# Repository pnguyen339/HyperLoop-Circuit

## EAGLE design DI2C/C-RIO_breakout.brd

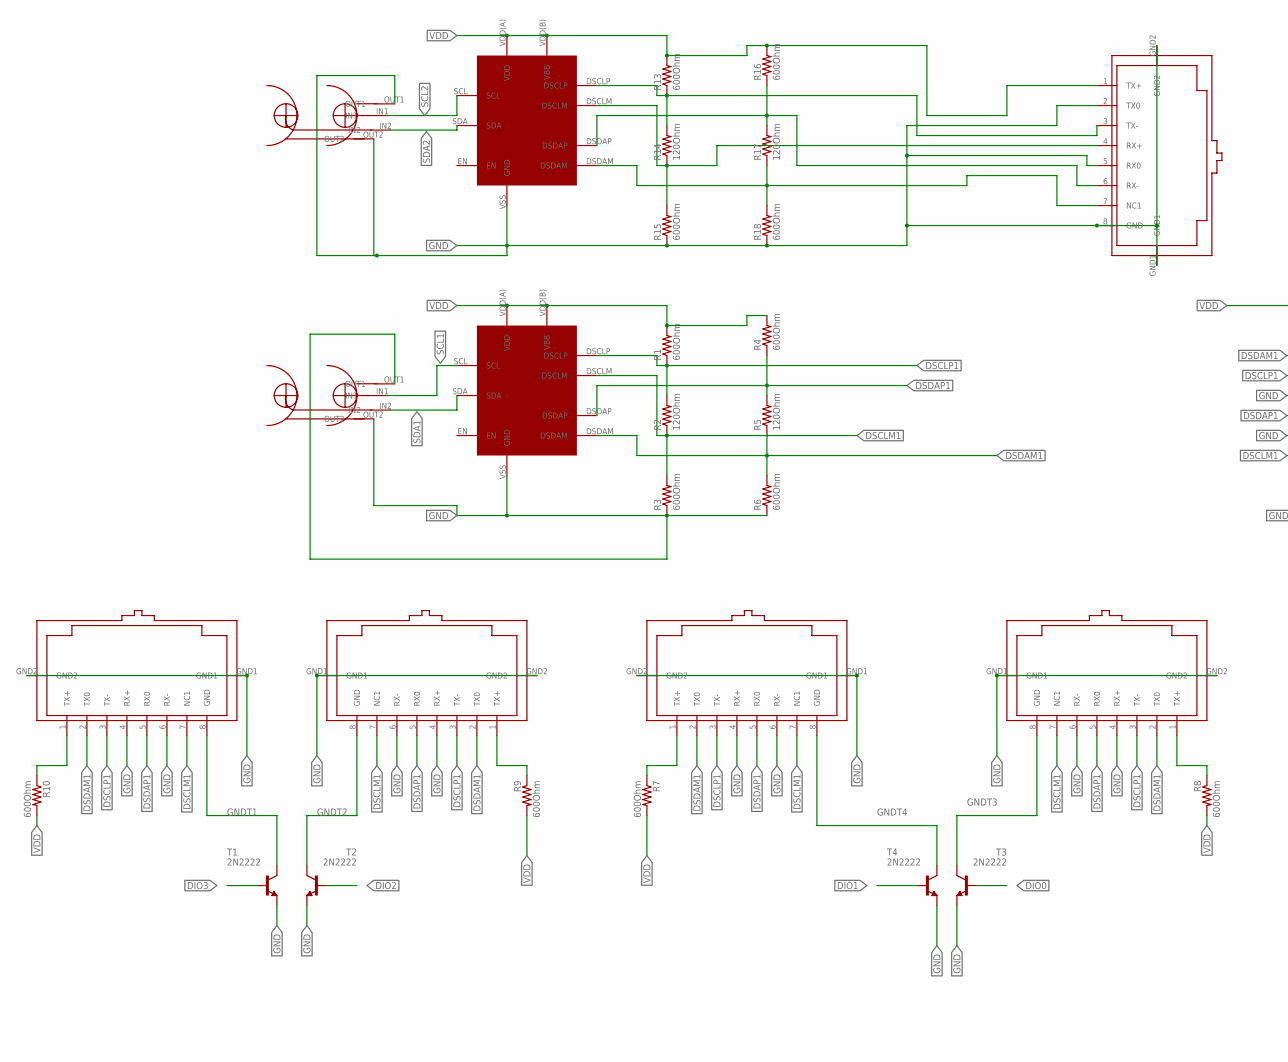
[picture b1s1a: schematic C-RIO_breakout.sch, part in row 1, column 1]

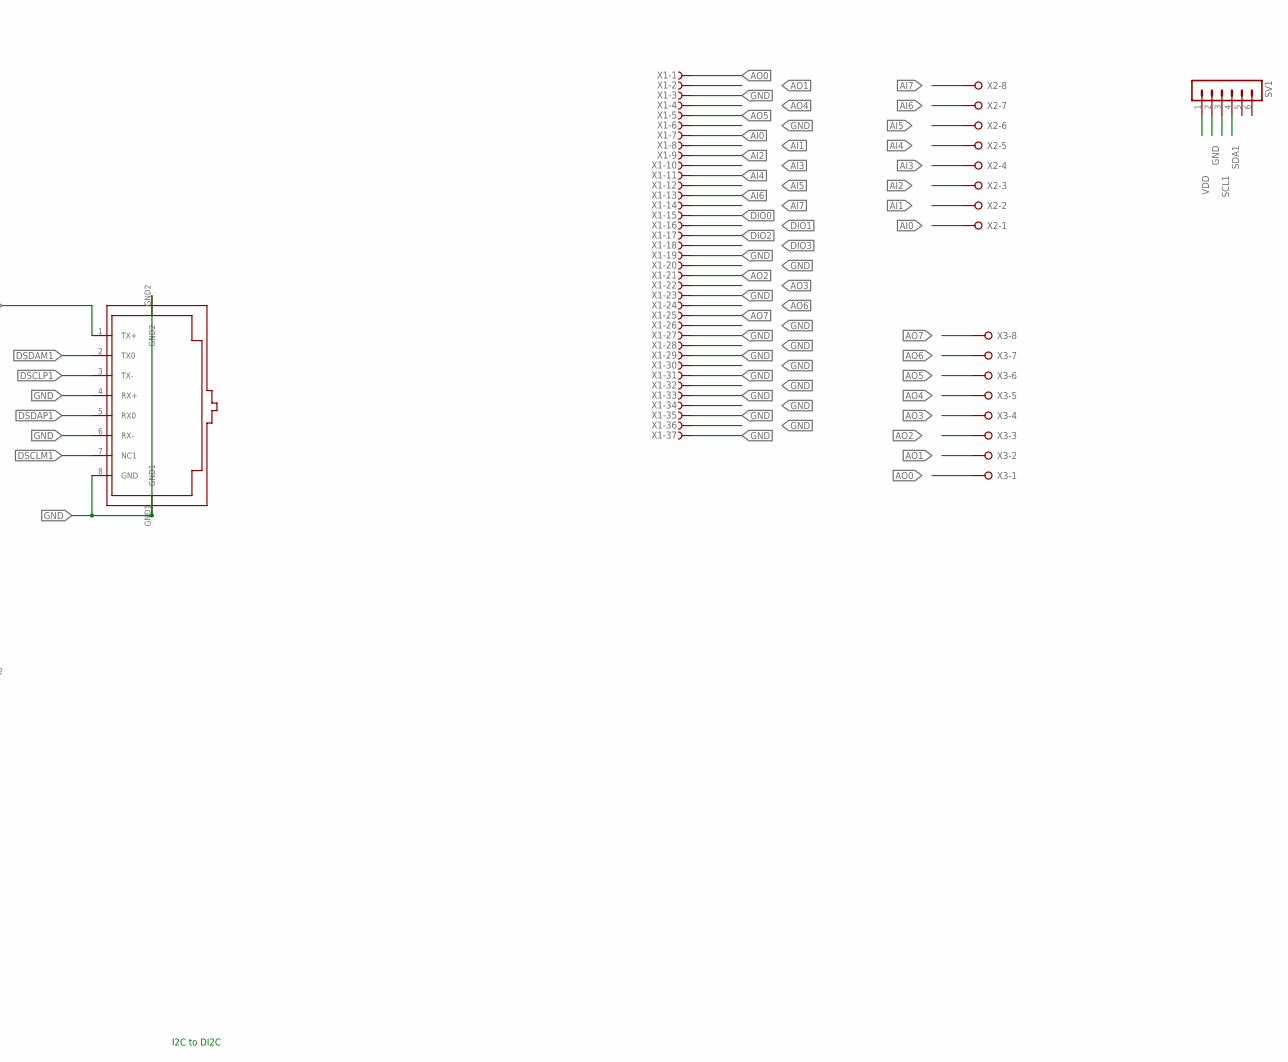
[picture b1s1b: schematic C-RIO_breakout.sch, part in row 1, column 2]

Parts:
COMMON: RJ45-8N4-B
R1, R3, R4, R6, R7, R8, R9, R10, R13, R15, R16, R18: 600Ohm; 0414/15
R2, R5, R14, R17: 120Ohm; 0414/15
SV1: MA06-1
T1, T2, T3, T4: 2N2222; TO18
TOF1, TOF2, TOF3, TOF4: RJ45-8N4-B
U$1, U$3: PCA9615
U$2, U$4: DUALBNC_CONNECTOR
U$6: RJ45-8N4-B
X1: F37HPS; F37HP
X2, X3: W237-08P; W237-8P

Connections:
AI0: X1.7, X2.1
AI1: X1.8, X2.2
AI2: X1.9, X2.3
AI3: X1.10, X2.4
AI4: X1.11, X2.5
AI5: X1.12, X2.6
AI6: X1.13, X2.7
AI7: X1.14, X2.8
AO0: X1.1, X3.1
AO1: X1.2, X3.2
AO2: X1.21, X3.3
AO3: X1.22, X3.4
AO4: X1.4, X3.5
AO5: X1.5, X3.6
AO6: X1.24, X3.7
AO7: X1.25, X3.8
DIO0: T3.2 (B), X1.15
DIO1: T4.2 (B), X1.16
DIO2: T2.2 (B), X1.17
DIO3: T1.2 (B), X1.18
DSCLM1: COMMON.7 (NC1), R2.1, R3.2, TOF1.7 (NC1), TOF2.7 (NC1), TOF3.7 (NC1), TOF4.7 (NC1), U$1.DSCLM
DSCLP1: COMMON.3 (TX-), R1.1, R2.2, TOF1.3 (TX-), TOF2.3 (TX-), TOF3.3 (TX-), TOF4.3 (TX-), U$1.DSCLP
DSDAM1: COMMON.2 (TX0), R5.1, R6.2, TOF1.2 (TX0), TOF2.2 (TX0), TOF3.2 (TX0), TOF4.2 (TX0), U$1.DSDAM
DSDAP1: COMMON.5 (RX0), TOF1.5 (RX0), TOF2.5 (RX0), TOF3.5 (RX0), TOF4.5 (RX0)
GND: COMMON.4 (RX+), COMMON.6 (RX-), COMMON.8 (GND), COMMON.GND1, COMMON.GND2, R3.1, R6.1, R15.1, R18.1, SV1.2, T1.1 (E), T2.1 (E), T3.1 (E), T4.1 (E), TOF1.4 (RX+), TOF1.6 (RX-), TOF2.4 (RX+), TOF2.6 (RX-), TOF3.4 (RX+), TOF3.6 (RX-), TOF4.4 (RX+), TOF4.6 (RX-), U$1.VSS (GND), U$2.OUT1, U$2.OUT2, U$3.VSS (GND), U$4.OUT1, U$4.OUT2, U$6.2 (TX0), U$6.5 (RX0), U$6.8 (GND), U$6.GND1, U$6.GND2, X1.3, X1.6, X1.19, X1.20, X1.23, X1.26, X1.27, X1.28, X1.29, X1.30, X1.31, X1.32, X1.33, X1.34, X1.35, X1.36, X1.37
GND2: TOF1.GND1, TOF1.GND2, TOF2.GND1, TOF2.GND2, TOF3.GND1, TOF3.GND2, TOF4.GND1, TOF4.GND2
GNDT1: T1.3 (C), TOF4.8 (GND)
GNDT2: T2.3 (C), TOF3.8 (GND)
GNDT3: T3.3 (C), TOF1.8 (GND)
GNDT4: T4.3 (C), TOF2.8 (GND)
unnamed: R4.1, R5.2, U$1.DSDAP
unnamed: R13.1, R14.2, U$3.DSCLP, U$6.3 (TX-)
unnamed: R14.1, R15.2, U$3.DSCLM, U$6.4 (RX+)
unnamed: R16.1, R17.2, U$3.DSDAP, U$6.6 (RX-)
unnamed: R17.1, R18.2, U$3.DSDAM, U$6.7 (NC1)
SCL1: SV1.3, U$1.SCL, U$4.IN1
SCL2: U$2.IN1, U$3.SCL
SDA1: SV1.4, U$1.SDA, U$4.IN2
SDA2: U$2.IN2, U$3.SDA
VDD: COMMON.1 (TX+), R1.2, R4.2, R7.1, R7.2, R8.1, R8.2, R9.1, R9.2, R10.1, R10.2, R13.2, R16.2, SV1.1, TOF1.1 (TX+), TOF2.1 (TX+), TOF3.1 (TX+), TOF4.1 (TX+), U$1.VDD(A) (VDD), U$1.VDD(B) (VBB), U$3.VDD(A) (VDD), U$3.VDD(B) (VBB), U$6.1 (TX+)

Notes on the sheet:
I2C to DI2C

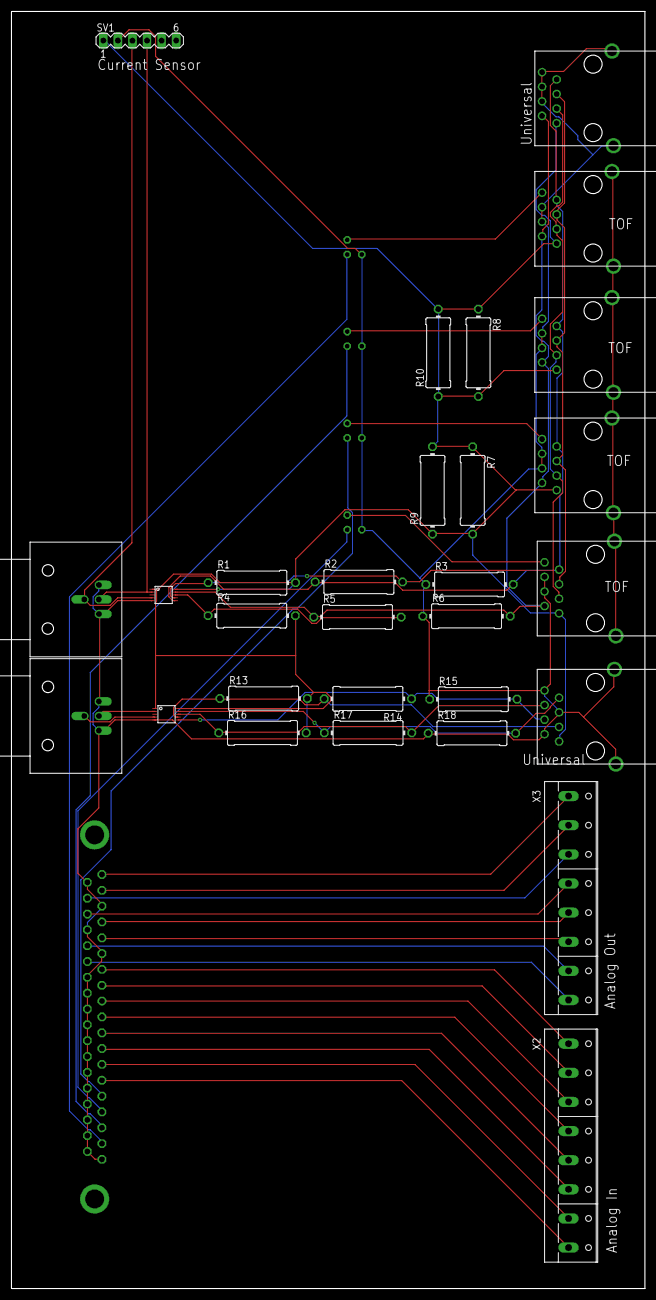
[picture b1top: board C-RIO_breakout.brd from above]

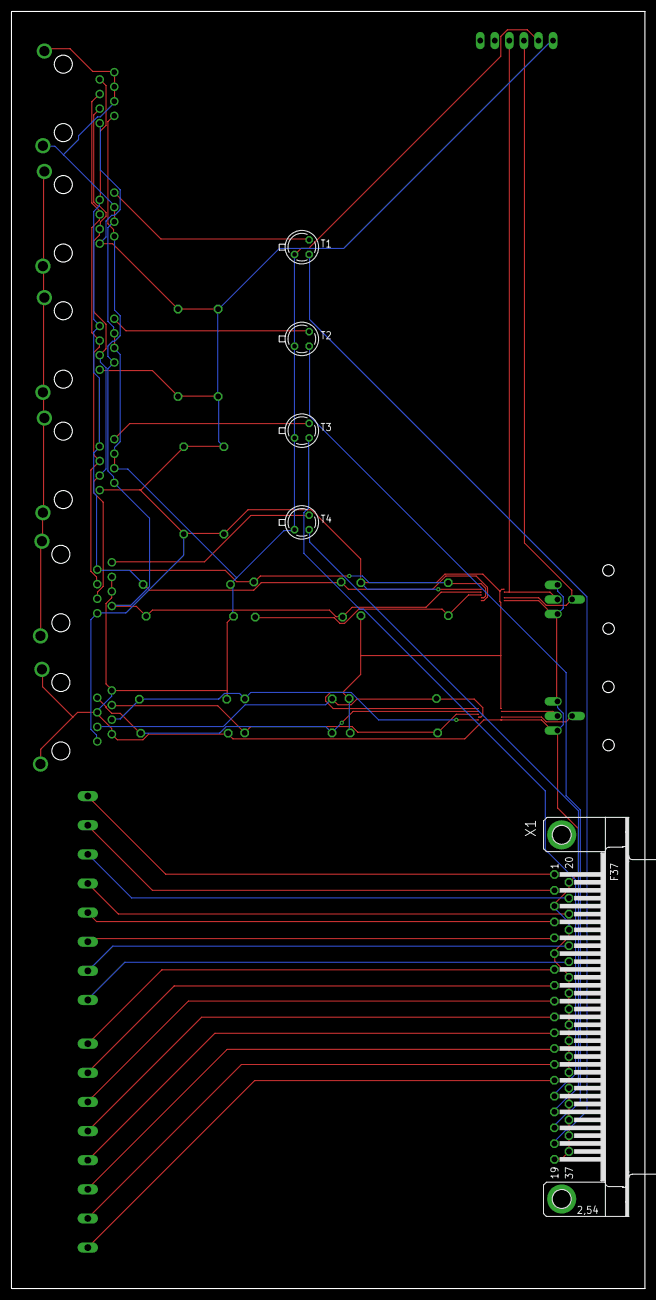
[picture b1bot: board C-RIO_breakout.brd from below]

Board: 2 copper layers, 110.5 x 222.7 mm, 34 parts (5 on the bottom side), 40 nets.

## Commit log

2018-04-21 update PCA9615
2018-05-11 finish i2c base master board
2018-06-02 update schmeatic
2018-06-07 added the lsave board
